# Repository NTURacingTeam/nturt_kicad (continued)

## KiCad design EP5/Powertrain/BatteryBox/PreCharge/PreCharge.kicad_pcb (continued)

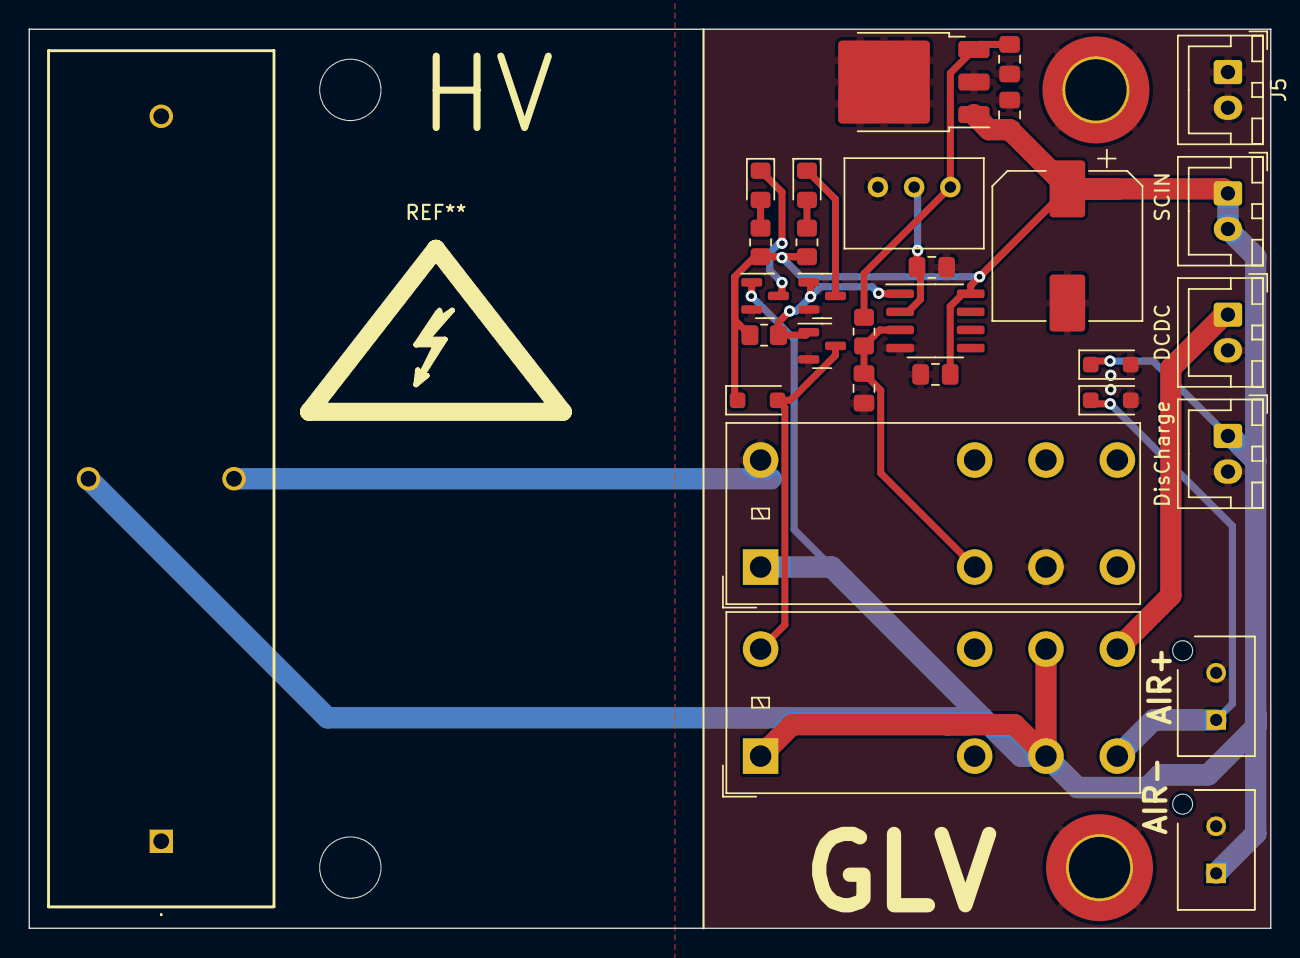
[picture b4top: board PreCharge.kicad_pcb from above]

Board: 2 copper layers, 87.0 x 63.0 mm, 34 parts (0 on the bottom side), 13 nets.

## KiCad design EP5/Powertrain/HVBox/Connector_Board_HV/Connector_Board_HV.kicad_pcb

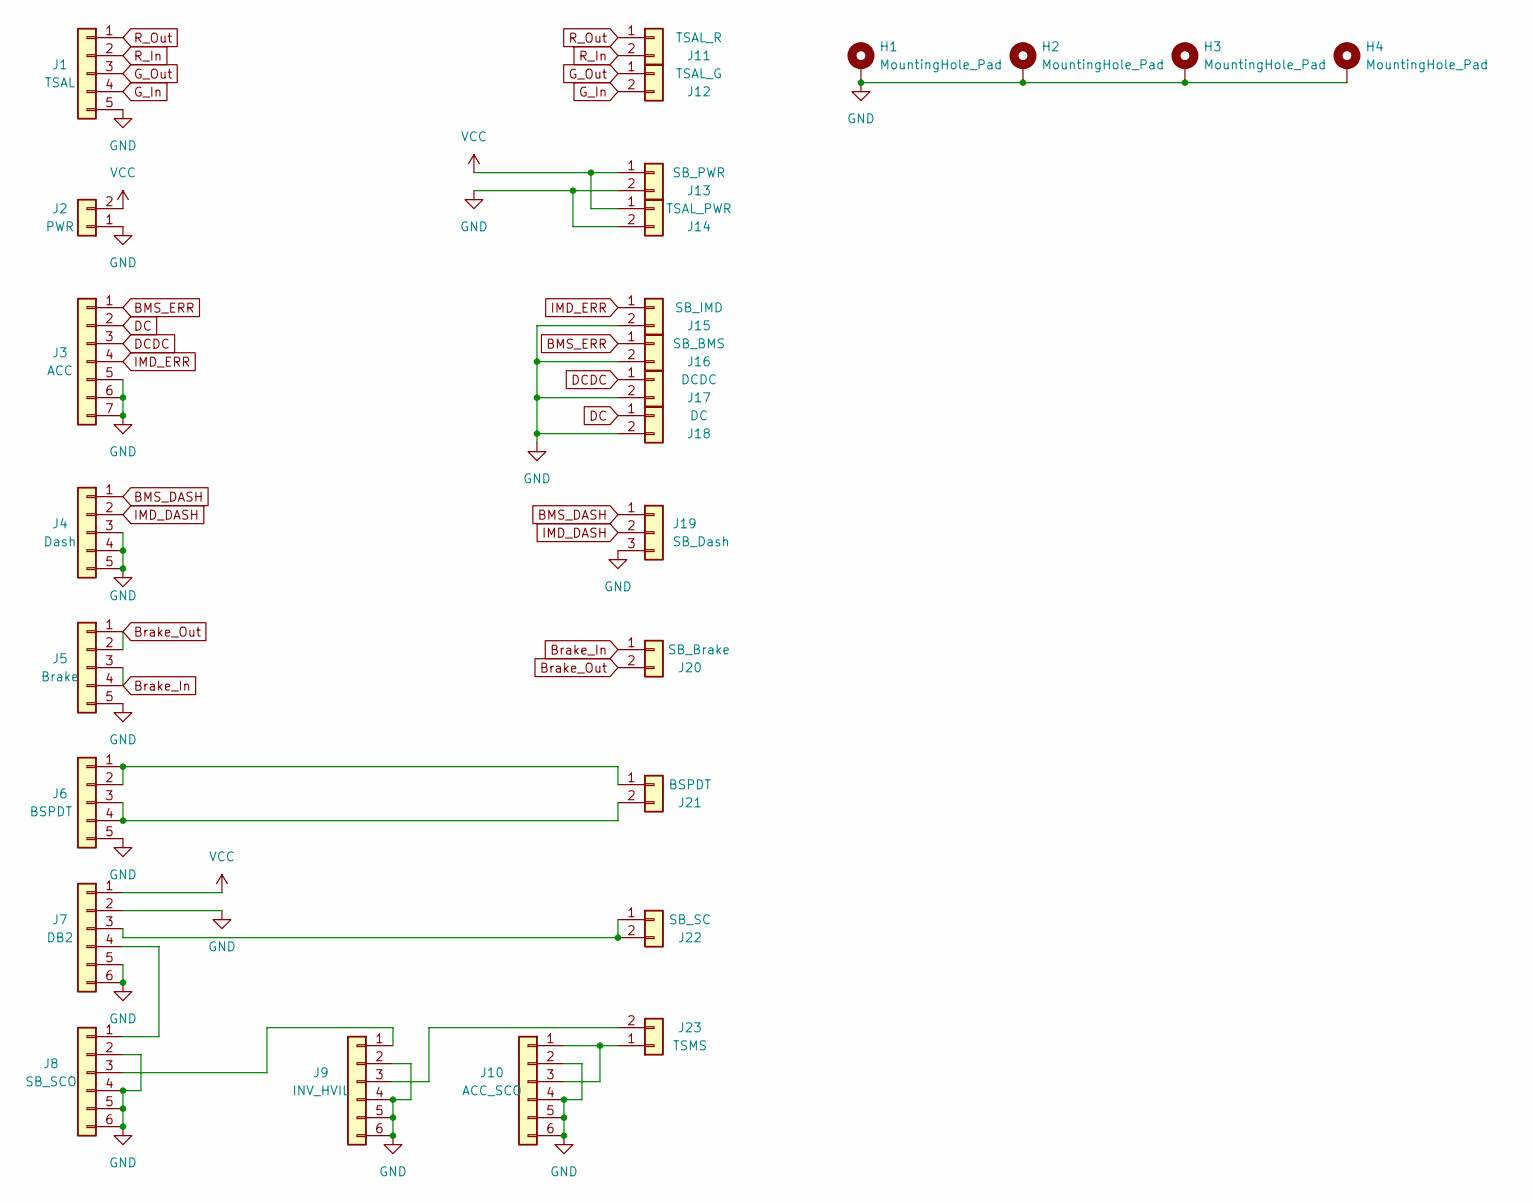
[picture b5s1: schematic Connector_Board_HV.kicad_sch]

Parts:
H1, H2, H3, H4: MountingHole_Pad; MountingHole_4.3mm_M4_DIN965_Pad_TopBottom
J1: TSAL; M8 2P 4P w Ground
J2: PWR; JST_VH_B2P-VH-B_1x02_P3.96mm_Vertical
J3: ACC; M8 5-6P w Ground
J4: Dash; M8 2P 4P w Ground
J5: Brake; M8 2P 4P w Ground
J6: BSPDT; M8 2P 4P w Ground
J7: DB2; M12 2-5P w Ground
J8: SB_SCO; M12 2-5P w Ground
J9: INV_HVIL; M12 2-5P w Ground
J10: ACC_SCO; M12 2-5P w Ground
J11: TSAL_R; JST_XH_B2B-XH-A_1x02_P2.50mm_Vertical
J12: TSAL_G; JST_XH_B2B-XH-A_1x02_P2.50mm_Vertical
J13: SB_PWR; JST_VH_B2P-VH-B_1x02_P3.96mm_Vertical
J14: TSAL_PWR; JST_XH_B2B-XH-A_1x02_P2.50mm_Vertical
J15: SB_IMD; JST_XH_B2B-XH-A_1x02_P2.50mm_Vertical
J16: SB_BMS; JST_XH_B2B-XH-A_1x02_P2.50mm_Vertical
J17: DCDC; JST_XH_B2B-XH-A_1x02_P2.50mm_Vertical
J18: DC; JST_XH_B2B-XH-A_1x02_P2.50mm_Vertical
J19: SB_Dash; JST_XH_B3B-XH-A_1x03_P2.50mm_Vertical
J20: SB_Brake; JST_XH_B2B-XH-A_1x02_P2.50mm_Vertical
J21: BSPDT; JST_XH_B2B-XH-A_1x02_P2.50mm_Vertical
J22: SB_SC; JST_XH_B2B-XH-A_1x02_P2.50mm_Vertical
J23: TSMS; JST_VH_B2P-VH-B_1x02_P3.96mm_Vertical

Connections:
BMS_DASH: J4.1, J19.1
BMS_ERR: J3.1, J16.1
Brake_In: J5.3, J5.4, J20.1
Brake_Out: J5.1, J5.2, J20.2
DC: J3.2, J18.1
DCDC: J3.3, J17.1
GND: H1.1, H2.1, H3.1, H4.1, J1.5, J2.1, J3.5, J3.6, J3.7, J4.3, J4.4, J4.5, J5.5, J6.5, J7.2, J7.5, J7.6, J8.2, J8.4, J8.5, J8.6, J9.2, J9.4, J9.5, J9.6, J10.2, J10.4, J10.5, J10.6, J13.2, J14.2, J15.2, J16.2, J17.2, J18.2, J19.3
G_In: J1.4, J12.2
G_Out: J1.3, J12.1
IMD_DASH: J4.2, J19.2
IMD_ERR: J3.4, J15.1
unnamed: J7.4, J8.1
unnamed: J8.3, J9.1
unnamed: J10.1, J10.3, J23.1
unnamed: J6.1, J6.2, J21.1
unnamed: J6.3, J6.4, J21.2
unnamed: J7.3, J22.1, J22.2
unnamed: J9.3, J23.2
R_In: J1.2, J11.2
R_Out: J1.1, J11.1
VCC: J2.2, J7.1, J13.1, J14.1

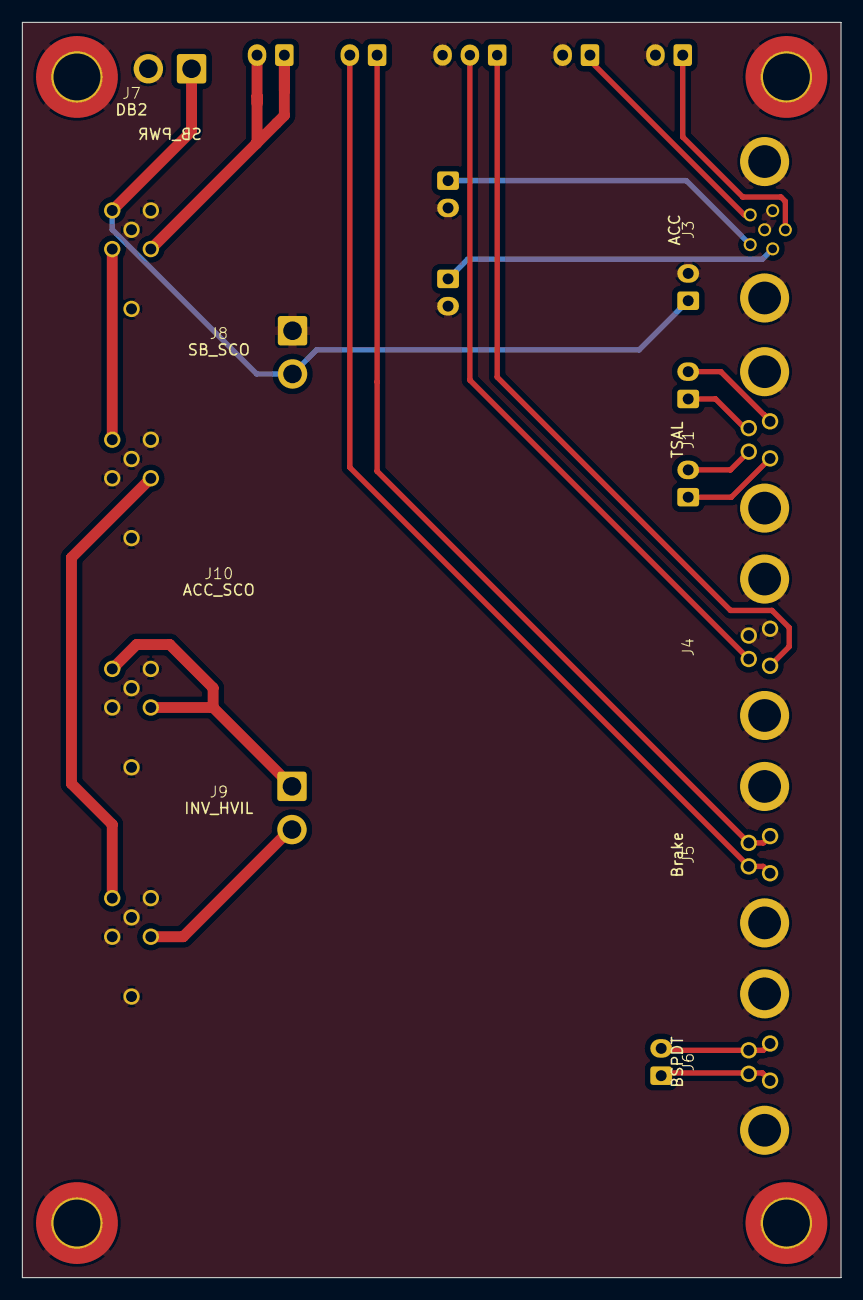
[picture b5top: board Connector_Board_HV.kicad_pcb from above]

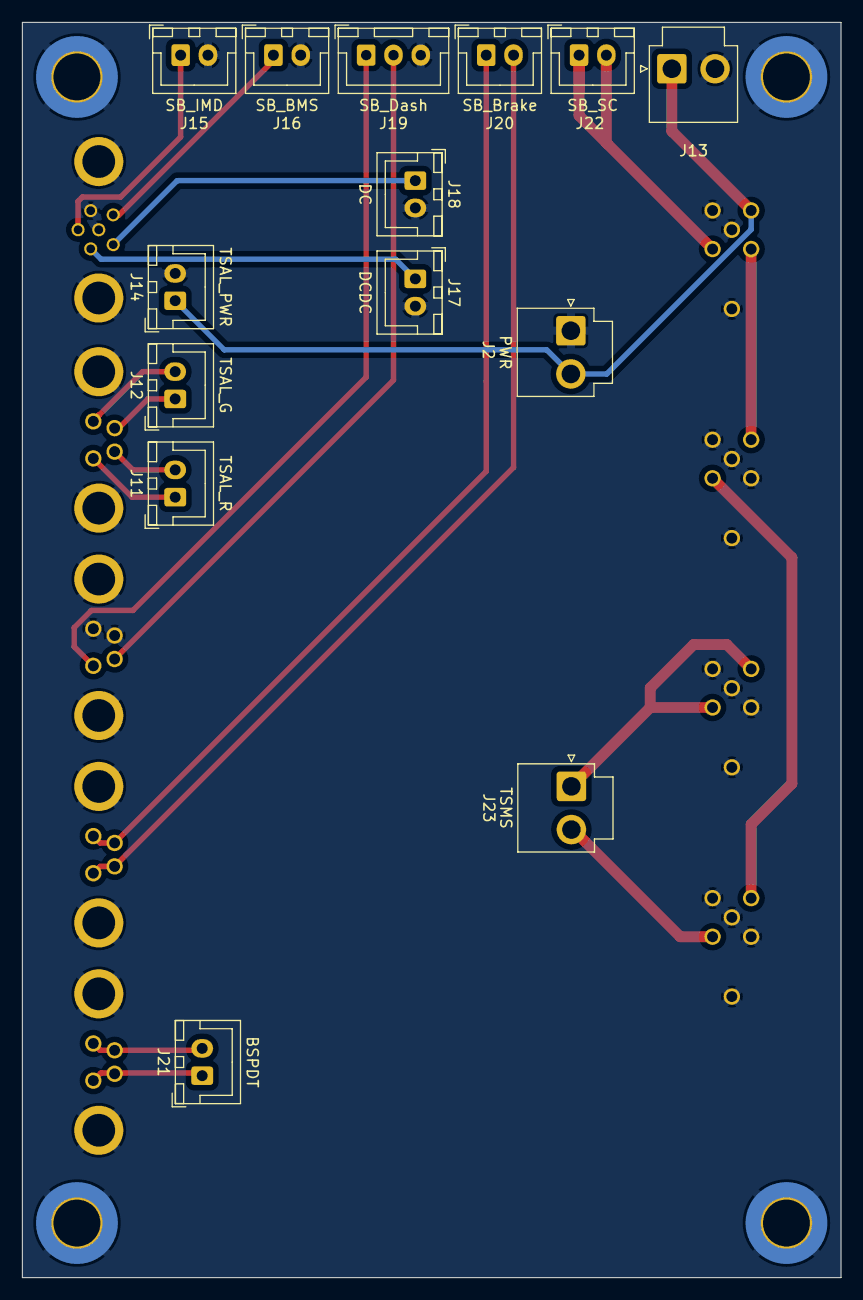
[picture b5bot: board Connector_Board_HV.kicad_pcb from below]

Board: 2 copper layers, 75.0 x 115.0 mm, 27 parts (14 on the bottom side), 21 nets.

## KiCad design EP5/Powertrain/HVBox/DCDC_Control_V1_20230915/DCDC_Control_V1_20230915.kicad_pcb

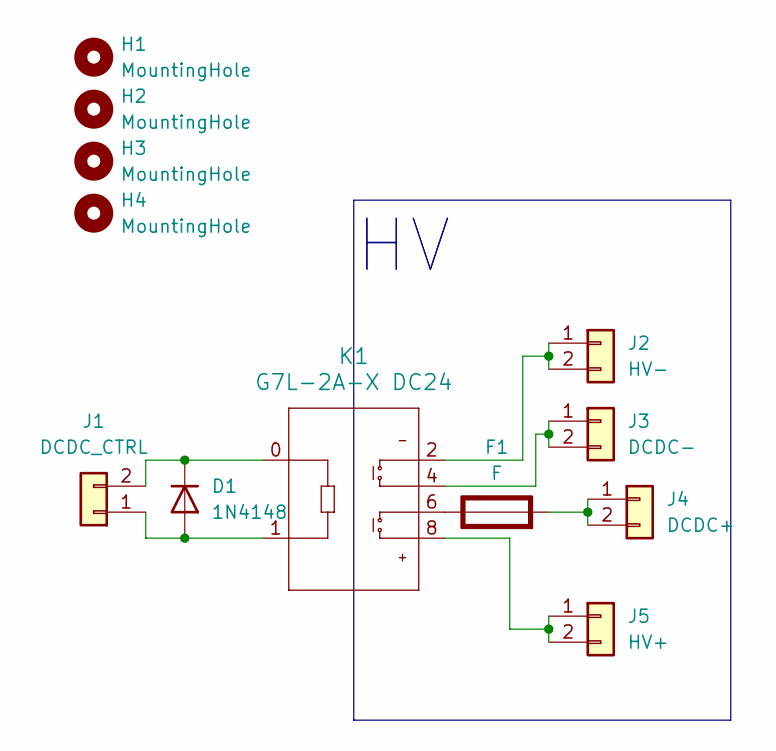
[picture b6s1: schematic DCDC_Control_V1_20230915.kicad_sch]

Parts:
D1: 1N4148; D_DO-35_SOD27_P7.62mm_Horizontal
F1: F; 65600001009; Rating W
H1, H2, H3, H4: MountingHole; MountingHole_4.3mm_M4_DIN965
J1: DCDC_CTRL; JST_XH_B2B-XH-A_1x02_P2.50mm_Vertical
J2: HV-; DF33C2P33DSA24
J3: DCDC-; DF33C2P33DSA24
J4: DCDC+; DF33C2P33DSA24
J5: HV+; DF33C2P33DSA24
K1: G7L-2A-X DC24; RELAY_G7L-2A-X_OMR

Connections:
unnamed: D1.2 (A), J1.1, K1.1
unnamed: D1.1 (K), J1.2, K1.0
unnamed: F1.1 (+), K1.6
unnamed: F1.2 (-), J4.1, J4.2
unnamed: J2.1, J2.2, K1.2
unnamed: J3.1, J3.2, K1.4
unnamed: J5.1, J5.2, K1.8

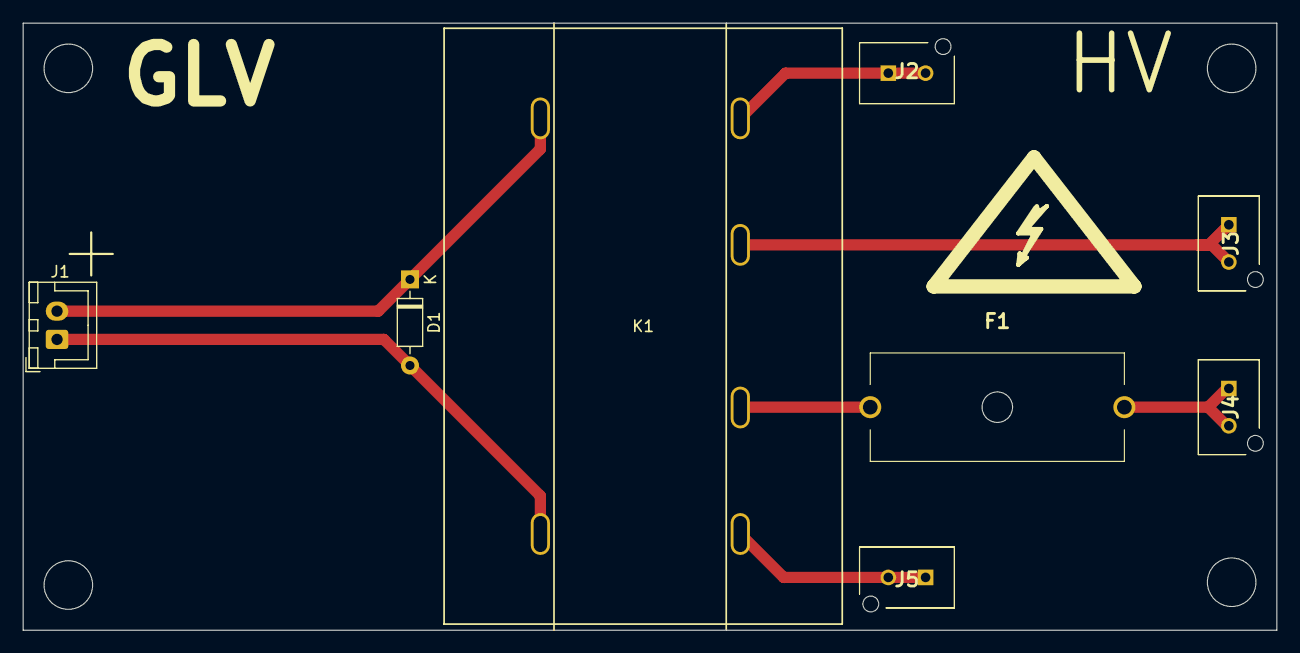
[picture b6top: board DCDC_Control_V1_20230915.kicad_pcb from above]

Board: 2 copper layers, 111.0 x 53.8 mm, 12 parts (0 on the bottom side), 7 nets.

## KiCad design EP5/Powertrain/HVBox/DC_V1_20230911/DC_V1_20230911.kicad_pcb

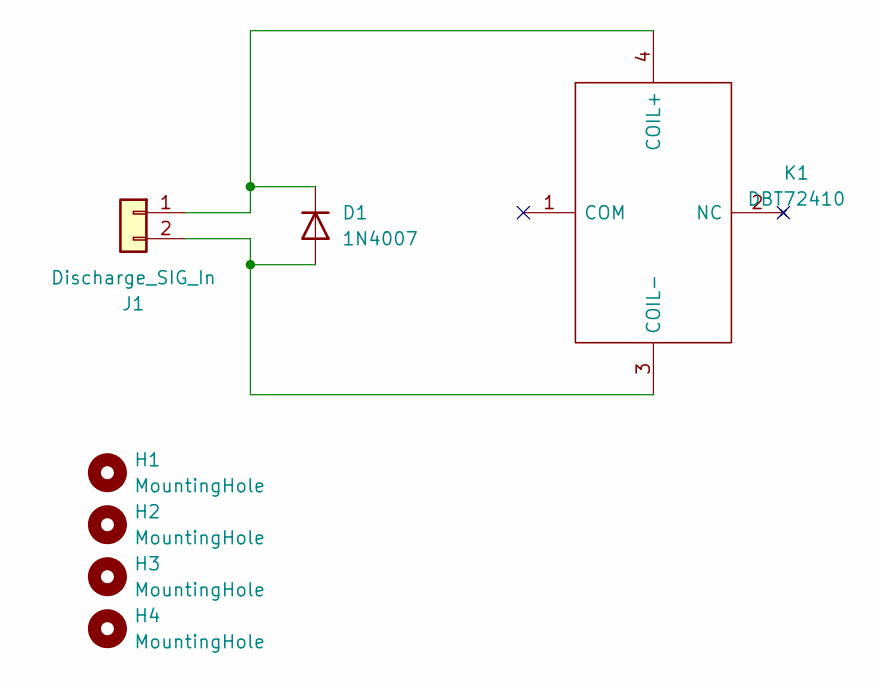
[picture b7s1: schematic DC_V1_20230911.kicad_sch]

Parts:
D1: 1N4007; D_DO-41_SOD81_P10.16mm_Horizontal
H1, H2, H3, H4: MountingHole; MountingHole_4.3mm_M4_DIN965
J1: Discharge_SIG_In; JST_XH_S2B-XH-A_1x02_P2.50mm_Horizontal
K1: DBT72410; Manufacturer_Part_Number DBT72410

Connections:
unnamed: D1.2 (A), J1.2, K1.3 (COIL-)
unnamed: D1.1 (K), J1.1, K1.4 (COIL+)

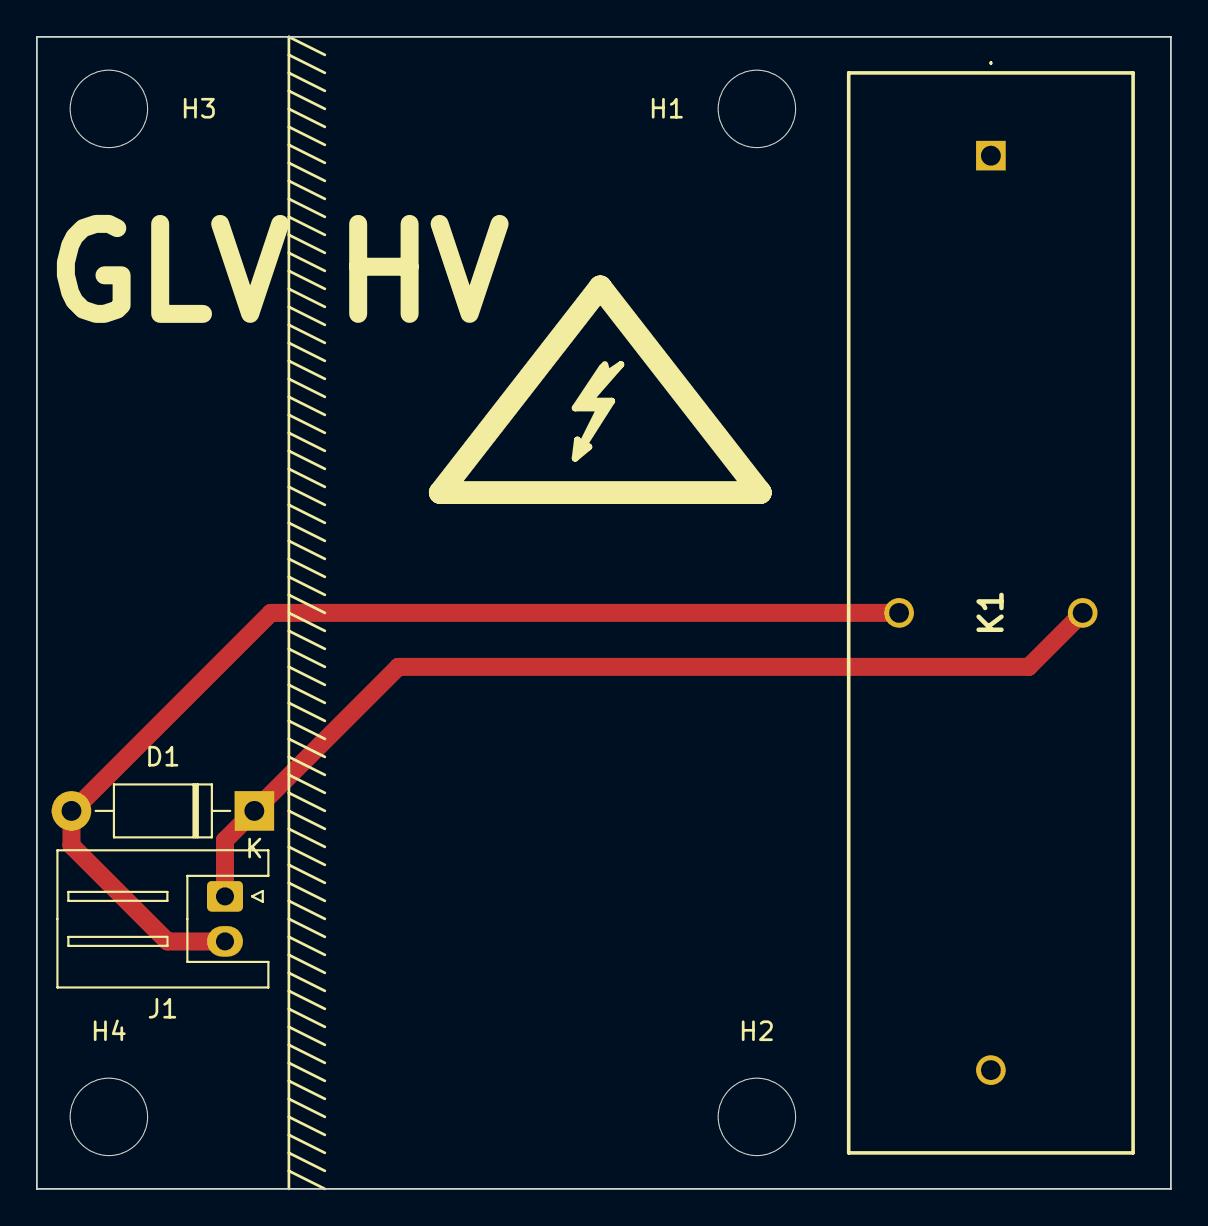
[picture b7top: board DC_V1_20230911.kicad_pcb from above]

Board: 2 copper layers, 63.0 x 64.0 mm, 7 parts (0 on the bottom side), 2 nets.

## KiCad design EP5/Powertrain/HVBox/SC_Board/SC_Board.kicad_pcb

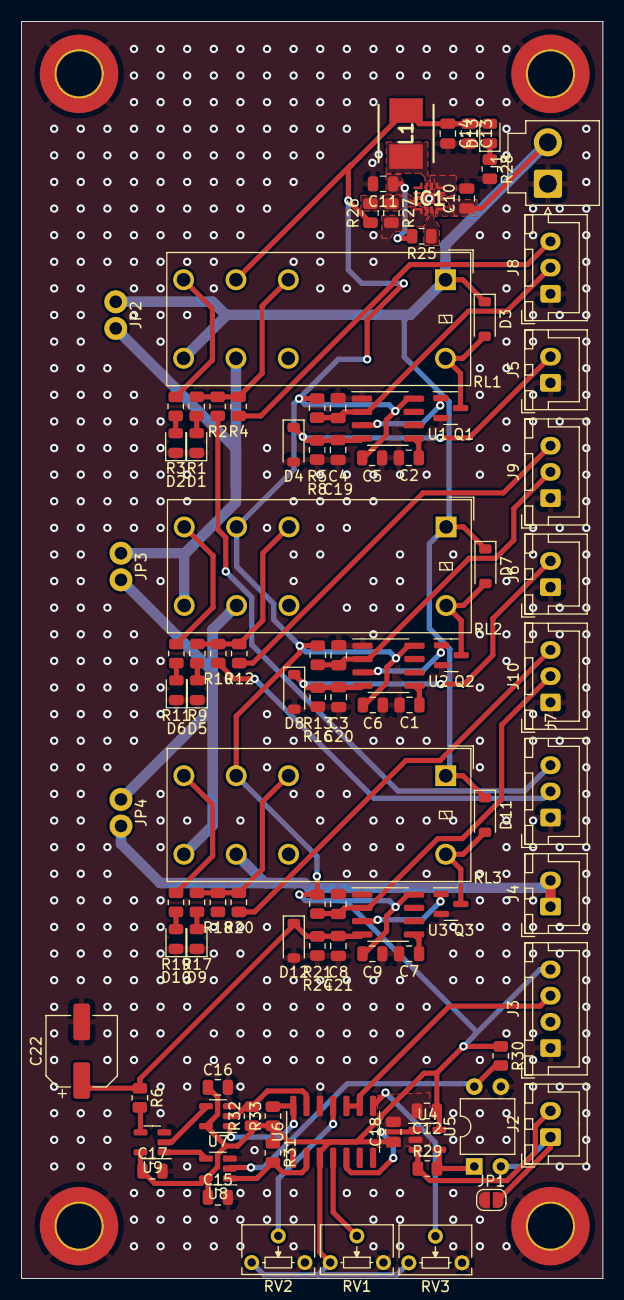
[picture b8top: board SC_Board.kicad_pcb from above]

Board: 2 copper layers, 55.5 x 120.0 mm, 101 parts (0 on the bottom side), 58 nets.

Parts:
C1, C2, C7: 10n; C_0805_2012Metric
C3, C4, C8, C12, C15, C16, C17, C18, C19, C20, C21: 100n; C_0805_2012Metric
C5, C6, C9: 10u; C_0805_2012Metric
C10: 10u 35V; C_0805_2012Metric
C11: 1u 16V; C_0805_2012Metric
C13, C14: 22u 16V; C_0805_2012Metric
C22: 220u; CP_Elec_6.3x4.9
D1, D5, D9: Red; LED_0805_2012Metric
D2, D6, D10: Green; LED_0805_2012Metric
D3, D7, D11: 4148; D_SOD-123
D4, D8, D12: BZV55C5V6; D_SOD-123
D13: 5VGood; LED_0805_2012Metric
H1, H2, H3, H4: MountingHole_Pad; MountingHole_4.3mm_M4_DIN965_Pad_TopBottom
IC1: LMQ66420MC5RXBRQ1; LMQ66430R5RXBR
J1: PWR; JST_VH_B2P-VH-B_1x02_P3.96mm_Vertical
J2: Brake_IN; JST_XH_B2B-XH-A_1x02_P2.50mm_Vertical
J3: I_Sen; JST_XH_B4B-XH-A_1x04_P2.50mm_Vertical
J4: SC_OUT; JST_XH_B2B-XH-A_1x02_P2.50mm_Vertical
J5: BMS_Fault; JST_XH_B2B-XH-A_1x02_P2.50mm_Vertical
J6: IMD_Fault; JST_XH_B2B-XH-A_1x02_P2.50mm_Vertical
J7: DASH_LED; JST_XH_B3B-XH-A_1x03_P2.50mm_Vertical
J8: BMS_BTN; JST_XH_B3B-XH-A_1x03_P2.50mm_Vertical
J9: IMD_BTN; JST_XH_B3B-XH-A_1x03_P2.50mm_Vertical
J10: BSPD_BTN; JST_XH_B3B-XH-A_1x03_P2.50mm_Vertical
JP1: SolderJumper_2_Open; SolderJumper-2_P1.3mm_Open_RoundedPad1.0x1.5mm
JP2, JP3, JP4: Jumper_2_Open; Jumper_P2.54mm_D1.2mm
L1: 4.7u 3A; INDPM5552X300N
Q1, Q2, Q3: 2N7002; SOT-23
R1, R3, R9, R11, R17, R19, R28: 1k; R_0805_2012Metric
R2, R4, R6, R10, R12, R18, R20: 220; R_0805_2012Metric
R5, R8, R13, R16, R21, R24, R25: 10k; R_0805_2012Metric
R26: 49.9k; R_0805_2012Metric
R27: 12.4k; R_0805_2012Metric
R29: 12.4; R_0805_2012Metric
R30: 1K; R_0805_2012Metric
R31, R32, R33: 10K; R_0805_2012Metric
RL1, RL2, RL3: G2RL-24-DC24; Relay_DPDT_Omron_G2RL-2
RV1: 10K; Potentiometer_Bourns_3266W_Vertical
RV2, RV3: 10k; Potentiometer_Bourns_3266W_Vertical
U1, U2, U3: NE555D; SOIC-8_3.9x4.9mm_P1.27mm
U4: INA180A1; SOT-23-5
U5: EL817; DIP-4_W7.62mm
U6: LM339; SOIC-14_3.9x8.7mm_P1.27mm
U7, U8: 74AHC1G32; SOT-23-5
U9: 74AHC1G00; SOT-23-5

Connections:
5V_PGood: IC1.14 (PG), R25.1
5V_SW: IC1.7 (SW), L1.1
+5V: C5.1, C6.1, C9.1, C12.1, C13.1, C14.1, C15.1, C16.1, C17.1, C18.1, D13.2 (A), J3.4, L1.2, R5.1, R13.1, R21.1, R26.1, R30.1, R31.1, R32.1, R33.1, RL1.11, RL2.11, RL3.11, RV1.1, RV2.1, RV3.1, U1.8 (VCC), U2.8 (VCC), U3.8 (VCC), U4.5 (V+), U6.3 (V+), U7.5 (VCC), U8.5 (VCC), U9.5 (VCC)
/BSPD/Brake_IN: J2.2, R29.1, U4.3 (+)
/BSPD/Brake_OUT: J2.1, JP1.2 (B), U5.2
/BSPD/Fault_OUT: C21.1, C22.1, D12.1 (K), R6.1, R24.1, U3.4 (R)
/BSPD/I_IN: J3.3, U6.9 (+), U6.10 (-)
/Latch_BMS/Fault_IN: C19.1, D4.1 (K), J5.2, R8.1, U1.4 (R)
/Latch_BMS/SC_OUT: JP2.2 (B), JP3.1 (A), RL1.21, RL2.24
/Latch_BSPD/SC_IN: JP3.2 (B), JP4.1 (A), RL2.21, RL3.24
/Latch_BSPD/SC_OUT: J4.1, J4.2, JP4.2 (B), RL3.21
/Latch_IMD/Fault_IN: C20.1, D8.1 (K), J6.2, R16.1, U2.4 (R)
BMS_BUTTON: J8.3, R4.2
BMS_DASH: J7.3, R2.2
BMS_RESET: C4.1, J8.2, R5.2, U1.2 (TR)
BSPD_BUTTON: J10.3, R20.2
BSPD_RESET: C8.1, J10.2, R21.2, U3.2 (TR)
GND: C1.2, C2.2, C3.2, C4.2, C5.2, C6.2, C7.2, C8.2, C9.2, C10.2, C11.2, C12.2, C13.2, C14.2, C15.2, C16.2, C17.2, C18.2, C19.2, C20.2, C21.2, C22.2, D1.1 (K), D2.1 (K), D4.2 (A), D5.1 (K), D6.1 (K), D8.2 (A), D9.1 (K), D10.1 (K), D12.2 (A), H1.1, H2.1, H3.1, H4.1, IC1.4 (NC_2), IC1.5 (NC_3), IC1.6 (PGND), IC1.12 (NC_5), IC1.13 (MODE/SYNC), IC1.15 (GND/DAP), IC1.17 (BOOT_2), IC1.19 (EN_2), J1.1, J3.1, J5.1, J6.1, J7.1, J8.1, J9.1, J10.1, JP1.1 (A), Q1.2 (S), Q2.2 (S), Q3.2 (S), R8.2, R16.2, R24.2, R27.2, R28.2, RV1.3, RV2.3, RV3.3, U1.1 (GND), U1.6 (THR), U2.1 (GND), U2.6 (THR), U3.1 (GND), U3.6 (THR), U4.2 (GND), U5.3, U6.12 (V-), U7.3 (GND), U8.3 (GND), U9.3 (GND)
IMD_BUTTON: J9.3, R12.2
IMD_DASH: J7.2, R10.2
IMD_RESET: C3.1, J9.2, R13.2, U2.2 (TR)
unnamed: D1.2 (A), R1.2
unnamed: D2.2 (A), R3.1
unnamed: D3.2 (A), Q1.3 (D), RL1.A2
unnamed: D5.2 (A), R9.2
unnamed: D6.2 (A), R11.1
unnamed: D7.2 (A), Q2.3 (D), RL2.A2
unnamed: D9.2 (A), R17.2
unnamed: D10.2 (A), R19.1
unnamed: D11.2 (A), Q3.3 (D), RL3.A2
unnamed: D13.1 (K), R28.1
unnamed: C11.1, IC1.10 (VCC), R25.2
unnamed: IC1.11 (VOUT/FB), R26.2, R27.1
unnamed: Q1.1 (G), U1.3 (Q)
unnamed: Q2.1 (G), U2.3 (Q)
unnamed: Q3.1 (G), U3.3 (Q)
unnamed: R1.1, R2.1, R4.1, RL1.12
unnamed: R3.2, RL1.14
unnamed: R6.2, U9.4
unnamed: R9.1, R10.1, R12.1, RL2.12
unnamed: R11.2, RL2.14
unnamed: R17.1, R18.1, R20.1, RL3.12
unnamed: R19.2, RL3.14
unnamed: R30.2, U5.4, U8.2
unnamed: R31.2, U6.2, U8.1
unnamed: R32.2, U6.13, U7.2
unnamed: R33.2, U6.14, U7.1
unnamed: C2.1, U1.5 (CV)
unnamed: C1.1, U2.5 (CV)
unnamed: C7.1, U3.5 (CV)
unnamed: R29.2, U4.4 (-), U5.1
unnamed: U4.1, U6.5 (+)
unnamed: RV1.2, U6.4 (-)
unnamed: RV2.2, U6.11 (+)
unnamed: RV3.2, U6.8 (-)
unnamed: U7.4, U9.2
unnamed: U8.4, U9.1
VBUS: C10.1, D3.1 (K), D7.1 (K), D11.1 (K), IC1.1 (EN_1), IC1.3 (VIN), IC1.16 (NC_6), J1.2, JP2.1 (A), RL1.24, RL1.A1, RL2.A1, RL3.A1
